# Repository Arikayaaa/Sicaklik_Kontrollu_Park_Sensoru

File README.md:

# Sicaklik_Kontrollu_Park_Sensoru
## Havadaki sıcaklığın ölçülmesi ve sesin havadaki hızının hesaplanarak mesafe sensörünün doğruluğunun stabilize edilmesi 
İlgili yazıma [buradan](https://medium.com/@sleymanarkaya/s%C4%B1cakl%C4%B1k-kontroll%C3%BC-park-sens%C3%B6r%C3%BC-811ae017df89) ulaşabilirsiniz.

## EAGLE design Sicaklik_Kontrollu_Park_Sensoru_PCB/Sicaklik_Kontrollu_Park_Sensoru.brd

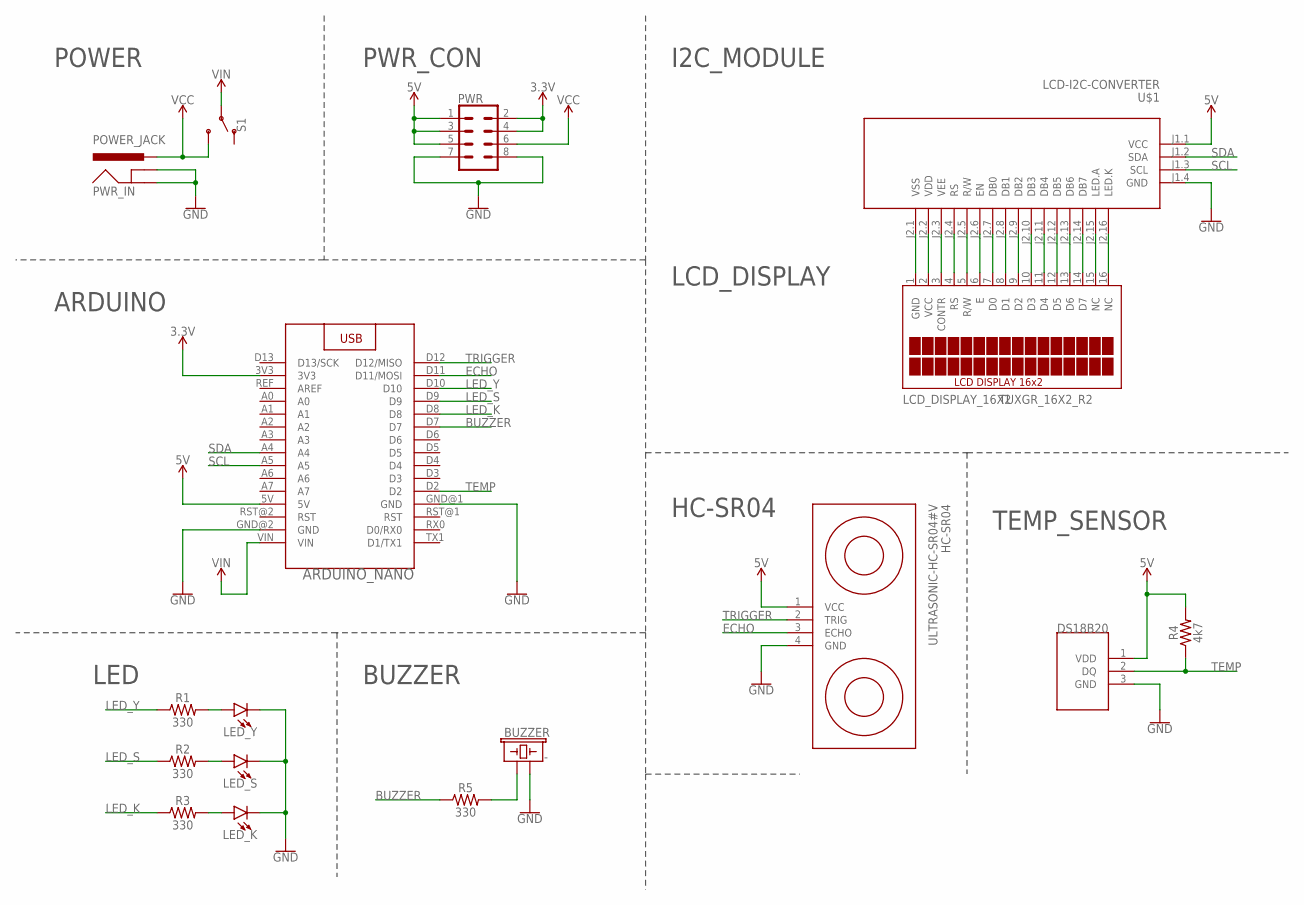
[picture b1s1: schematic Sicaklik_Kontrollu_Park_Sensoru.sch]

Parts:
ARDUINO_NANO: ARDUINO_NANO
BUZZER: -; BUZZER-12MM
DS18B20: DS18B20; TO-92
HC-SR04: ULTRASONIC-HC-SR04#V
LCD_DISPLAY_16X2: TUXGR_16X2_R2
LED_K: LED3MM; LED_3MM
LED_S: LED3MM; LED_3MM
LED_Y: LED3MM; LED_3MM
PWR: CONN_04X2; 2X4
PWR_IN: POWER_JACK; POWER_JACK_PTH
R1, R2, R3, R5: 330; AXIAL-0.3
R4: 4k7; AXIAL-0.3
S1: SWITCH-SPDT-SMD-RIGHT-ANGLE; SWITCH_SPST_SMD_A
U$1: LCD-I2C-CONVERTER

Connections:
3.3V: ARDUINO_NANO.3V3, PWR.2, PWR.4
5V: ARDUINO_NANO.5V, DS18B20.1 (VDD), HC-SR04.1 (VCC), PWR.1, PWR.3, PWR.5, R4.P$2 (2), U$1.J1.1 (VCC)
BUZZER: ARDUINO_NANO.D7, R5.P$1 (1)
ECHO: ARDUINO_NANO.D11 (D11/MOSI), HC-SR04.3 (ECHO)
GND: ARDUINO_NANO.GND@1 (GND), ARDUINO_NANO.GND@2 (GND), BUZZER.- (2), DS18B20.3 (GND), HC-SR04.4 (GND), LED_K.K (C), LED_S.K (C), LED_Y.K (C), PWR.7, PWR.8, PWR_IN.GND, PWR_IN.GNDBREAK, U$1.J1.4 (GND)
LED_K: ARDUINO_NANO.D8, R3.P$1 (1)
LED_S: ARDUINO_NANO.D9, R2.P$1 (1)
LED_Y: ARDUINO_NANO.D10, R1.P$1 (1)
unnamed: LCD_DISPLAY_16X2.16 (NC), U$1.J2.16 (LED.K)
unnamed: LCD_DISPLAY_16X2.15 (NC), U$1.J2.15 (LED.A)
unnamed: LCD_DISPLAY_16X2.14 (D7), U$1.J2.14 (DB7)
unnamed: LCD_DISPLAY_16X2.13 (D6), U$1.J2.13 (DB6)
unnamed: LCD_DISPLAY_16X2.12 (D5), U$1.J2.12 (DB5)
unnamed: LCD_DISPLAY_16X2.11 (D4), U$1.J2.11 (DB4)
unnamed: LCD_DISPLAY_16X2.10 (D3), U$1.J2.10 (DB3)
unnamed: LCD_DISPLAY_16X2.9 (D2), U$1.J2.9 (DB2)
unnamed: LCD_DISPLAY_16X2.8 (D1), U$1.J2.8 (DB1)
unnamed: LCD_DISPLAY_16X2.7 (D0), U$1.J2.7 (DB0)
unnamed: LCD_DISPLAY_16X2.6 (E), U$1.J2.6 (EN)
unnamed: LCD_DISPLAY_16X2.5 (R/W), U$1.J2.5 (R/W)
unnamed: LCD_DISPLAY_16X2.4 (RS), U$1.J2.4 (RS)
unnamed: LCD_DISPLAY_16X2.3 (CONTR), U$1.J2.3 (VEE)
unnamed: LCD_DISPLAY_16X2.2 (VCC), U$1.J2.2 (VDD)
unnamed: LCD_DISPLAY_16X2.1 (GND), U$1.J2.1 (VSS)
unnamed: BUZZER.+ (1), R5.P$2 (2)
unnamed: LED_Y.A, R1.P$2 (2)
unnamed: LED_S.A, R2.P$2 (2)
unnamed: LED_K.A, R3.P$2 (2)
SCL: ARDUINO_NANO.A5, U$1.J1.3 (SCL)
SDA: ARDUINO_NANO.A4, U$1.J1.2 (SDA)
TEMP: ARDUINO_NANO.D2, DS18B20.2 (DQ), R4.P$1 (1)
TRIGGER: ARDUINO_NANO.D12 (D12/MISO), HC-SR04.2 (TRIG)
VCC: PWR.6, PWR_IN.PWR, S1.3 (S)
VIN: ARDUINO_NANO.VIN, S1.2

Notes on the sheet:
POWER
PWR_CON
BUZZER
HC-SR04
LED
ARDUINO
LCD_DISPLAY
TEMP_SENSOR
I2C_MODULE

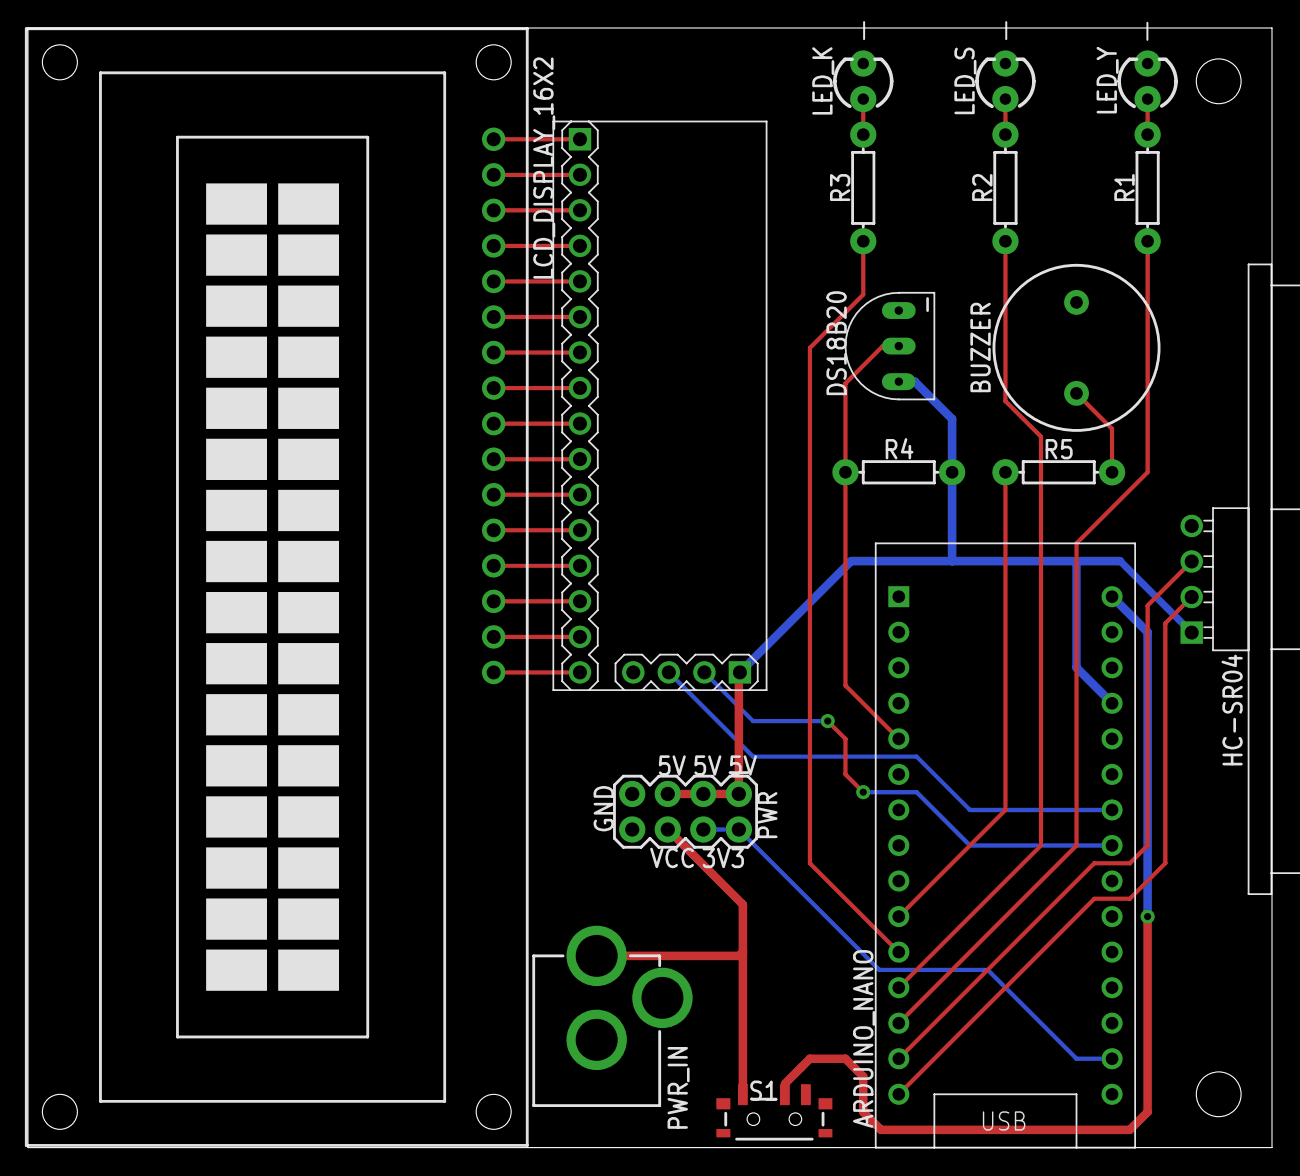
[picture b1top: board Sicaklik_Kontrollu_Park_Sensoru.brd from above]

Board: 2 copper layers, 88.9 x 80.0 mm, 17 parts (0 on the bottom side), 34 nets.

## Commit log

2022-05-20 v1.00
    Project documents were added
2022-05-23 v1.01
    Dosyalar düzenlendi.

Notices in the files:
parts and their libraries:
SparkFun-Connectors: Licensing: Creative Commons ShareAlike 4.0 International - https://creativecommons.org/licenses/by-sa/4.0
diy-modules: Released under the Creative Commons Attribution 4.0 International License: http://creativecommons.org/licenses/by/4.0
